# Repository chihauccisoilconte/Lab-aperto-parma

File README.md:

# plant_sounds_effects

Questa repository contiene tutti i files necessari per ricostruire il progetto "Plants Sound Effects", realizzato per il Laboratorio Aperto di PArma nel 2022

La repository contiene:

- Schematico e codice del circuito (utilizzabile con l'Arduino IDE) 
- Modello 3D del vaso (utilizzabile con FreeCAD)
- File SVG del pannello frontale del dispositivo (utilizzabile con InkScape)
- PCB Design (utilizzabile con KiCAD)

Maggiori info:
https://www.laboratoriaperti.it/parma
https://officineonoff.com/

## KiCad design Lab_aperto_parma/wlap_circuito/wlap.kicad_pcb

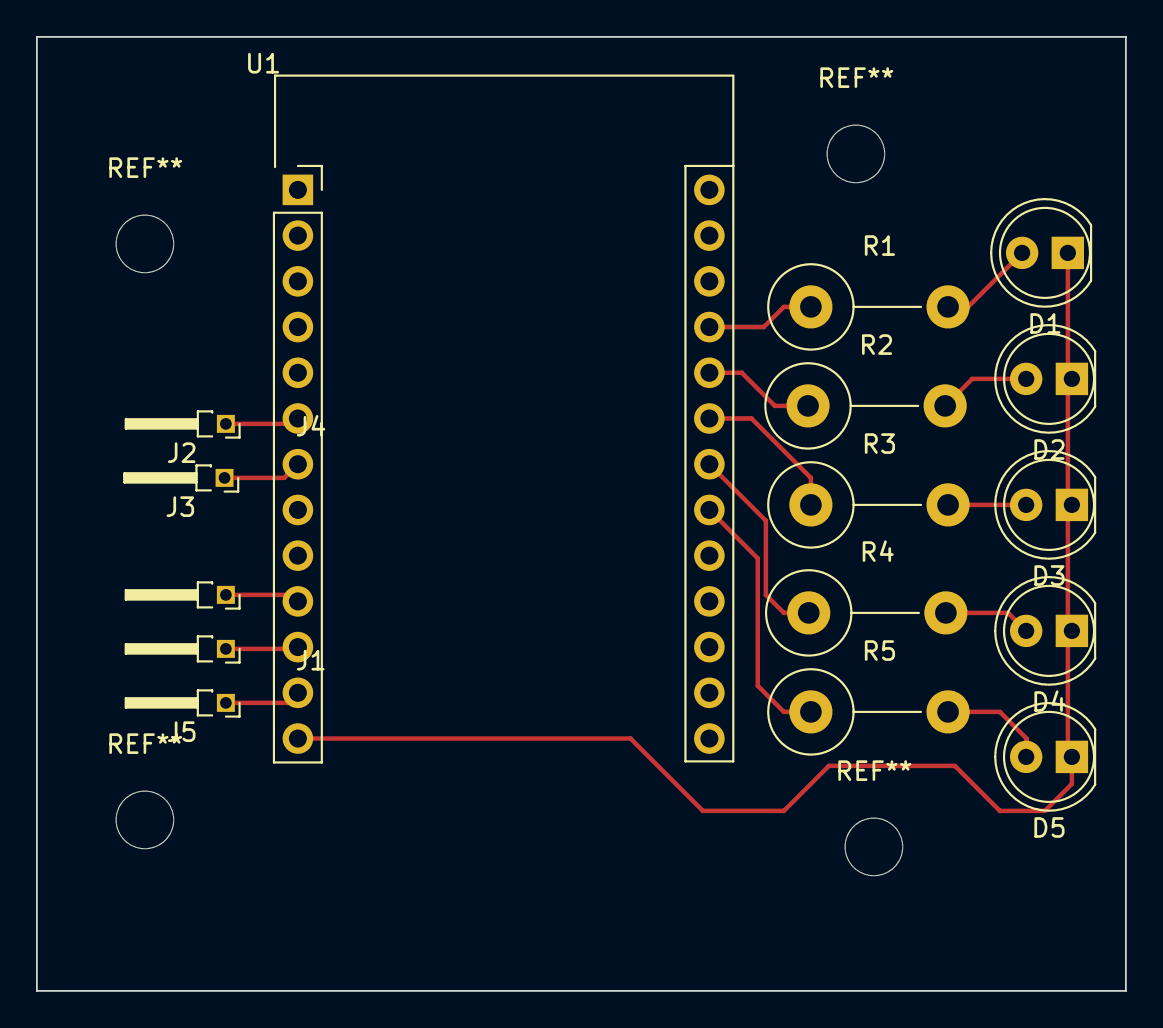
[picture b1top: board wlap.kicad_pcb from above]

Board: 2 copper layers, 60.5 x 53.0 mm, 16 parts (0 on the bottom side), 16 nets.

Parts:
D1, D2, D3, D4, D5: LED; LED_D5.0mm
J1, J2, J3, J4, J5: Conn_01x01_Female; PinHeader_1x01_P1.27mm_Horizontal
R1, R2, R3, R4, R5: R; R_Axial_DIN0414_L11.9mm_D4.5mm_P7.62mm_Vertical
U1: esp32_wemos_lolin32_lite

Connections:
unnamed: D1.1 (K), D2.1 (K), D3.1 (K), D4.1 (K), D5.1 (K), U1.13 (GND)
unnamed: D1.2 (A), R1.2
unnamed: D2.2 (A), R2.2
unnamed: D3.2 (A), R3.2
unnamed: D4.2 (A), R4.2
unnamed: D5.2 (A), R5.2
unnamed: J1.1, U1.11 (14)
unnamed: J2.1, U1.6 (32)
unnamed: J3.1, U1.7 (33)
unnamed: J4.1, U1.10 (27)
unnamed: J5.1, U1.12
unnamed: R1.1, U1.23
unnamed: R2.1, U1.22 (18)
unnamed: R3.1, U1.21 (5)
unnamed: R4.1, U1.20 (17)
unnamed: R5.1, U1.19 (16)
